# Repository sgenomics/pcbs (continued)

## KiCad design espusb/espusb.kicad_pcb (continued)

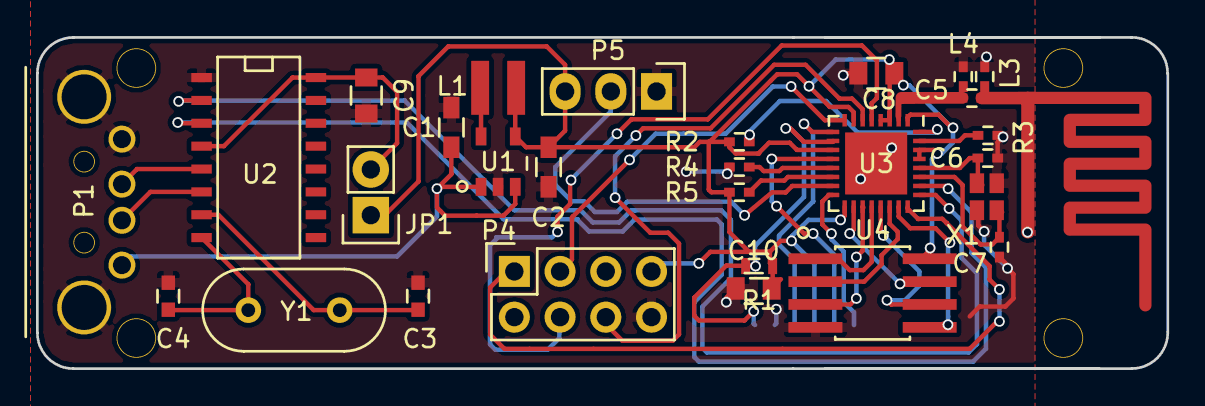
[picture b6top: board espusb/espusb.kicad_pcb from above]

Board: 2 copper layers, 62.8 x 18.4 mm, 30 parts (1 on the bottom side), 34 nets.

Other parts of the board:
svg2mod: G***; svg2mod
